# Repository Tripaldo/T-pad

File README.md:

# T-pad
my macropad, it has 8 buttons with macros that open apps and sites. every button has one or two led's linked to it so that they light up when the button is pressed. 

# Features
- 3d printed case
- led's linked to keys
- 8 keys
- simple python code with shortcuts to programs and sites

# CAD model
everything is held togheter by just 4 M3 bolts
the printed pieces are 2 and once the switches are soldered the keycaps will fit perfectly without any elevations.

made in fusion360.

# pcb
my pcb is very simple and made in KiCad.

this is the schematic:

this is the pcb:

# firmware
it uses KMK for a beginner friendly firmware.
- all 8 keys is a macro for apps and sites
- the firmware is easy to change so that everyone can change the macro's to whatever they like
- every button lights up the led near it
changes may be made in the future

# BOM
components needed for the hackpad (T-Pad)
- 8x cherry mx switches
- 8x dsa keycaps
- 4x M3 x 16 mm SHCS
- 12x SK6812 MINI
- 1x XIAO RP2040
- 1x case (only 3d printed parts)
  no need for diodes as it does not use a matrix but single digital pins
# extra
i have no idea what to tell you but it's my first project ever and hope it inspire someone

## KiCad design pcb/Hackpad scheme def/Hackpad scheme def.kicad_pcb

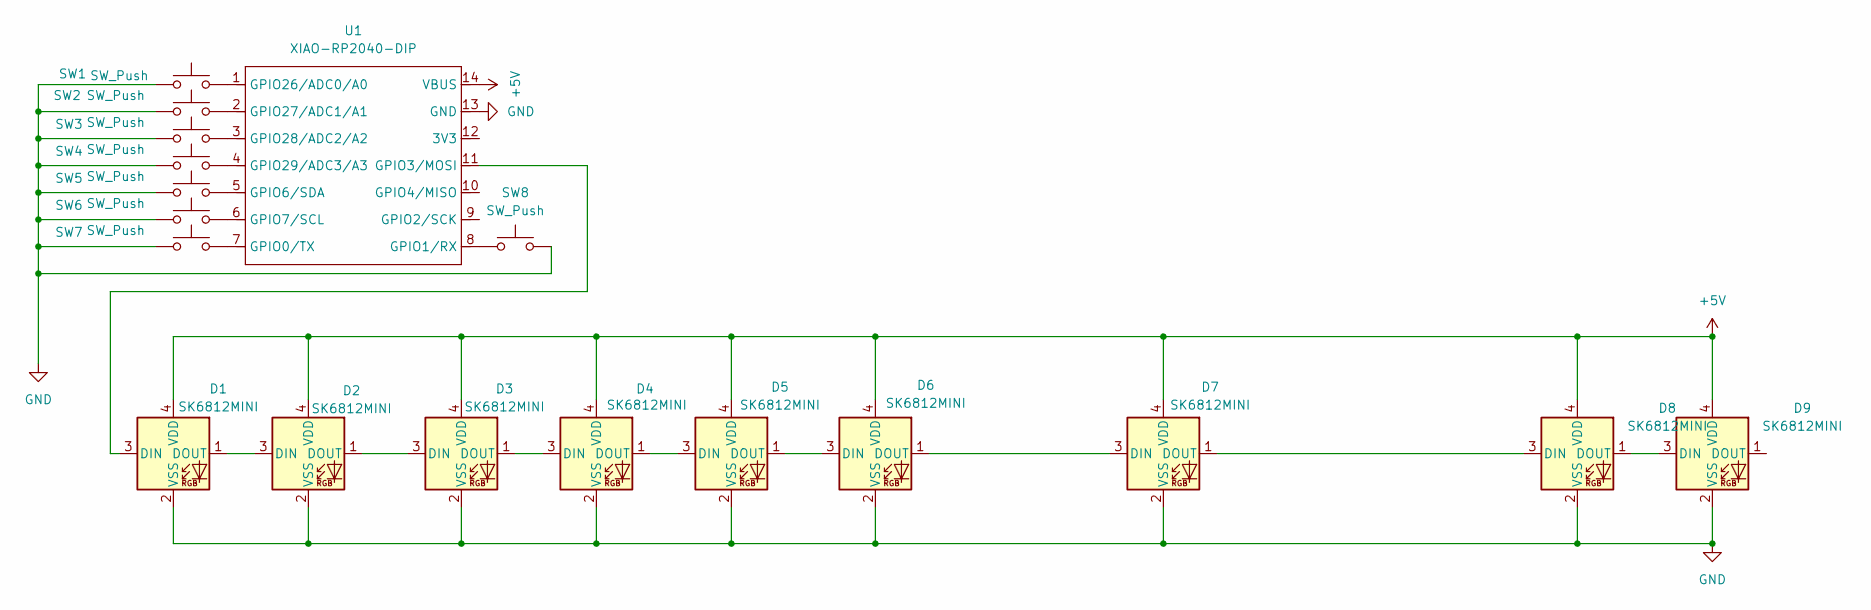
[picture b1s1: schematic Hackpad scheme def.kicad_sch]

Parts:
D1, D2, D3, D4, D5, D6, D7, D8, D9: SK6812MINI; LED_SK6812MINI_PLCC4_3.5x3.5mm_P1.75mm
SW1, SW2, SW3, SW4, SW5, SW6, SW7, SW8: SW_Push; SW_Cherry_MX_1.00u_PCB
U1: XIAO-RP2040-DIP

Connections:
+5V: D1.4 (VDD), D2.4 (VDD), D3.4 (VDD), D4.4 (VDD), D5.4 (VDD), D6.4 (VDD), D7.4 (VDD), D8.4 (VDD), D9.4 (VDD), U1.14 (VBUS)
GND: D1.2 (VSS), D2.2 (VSS), D3.2 (VSS), D4.2 (VSS), D5.2 (VSS), D6.2 (VSS), D7.2 (VSS), D8.2 (VSS), D9.2 (VSS), SW1.1, SW2.1, SW3.1, SW4.1, SW5.1, SW6.1, SW7.1, SW8.2, U1.13 (GND)
unnamed: D1.3 (DIN), U1.11 (GPIO3/MOSI)
unnamed: D1.1 (DOUT), D2.3 (DIN)
unnamed: D2.1 (DOUT), D3.3 (DIN)
unnamed: D3.1 (DOUT), D4.3 (DIN)
unnamed: D4.1 (DOUT), D5.3 (DIN)
unnamed: D5.1 (DOUT), D6.3 (DIN)
unnamed: D6.1 (DOUT), D7.3 (DIN)
unnamed: D7.1 (DOUT), D8.3 (DIN)
unnamed: D8.1 (DOUT), D9.3 (DIN)
unnamed: SW7.2, U1.7 (GPIO0/TX)
unnamed: SW8.1, U1.8 (GPIO1/RX)
unnamed: SW5.2, U1.5 (GPIO6/SDA)
unnamed: SW6.2, U1.6 (GPIO7/SCL)
unnamed: SW1.2, U1.1 (GPIO26/ADC0/A0)
unnamed: SW2.2, U1.2 (GPIO27/ADC1/A1)
unnamed: SW3.2, U1.3 (GPIO28/ADC2/A2)
unnamed: SW4.2, U1.4 (GPIO29/ADC3/A3)

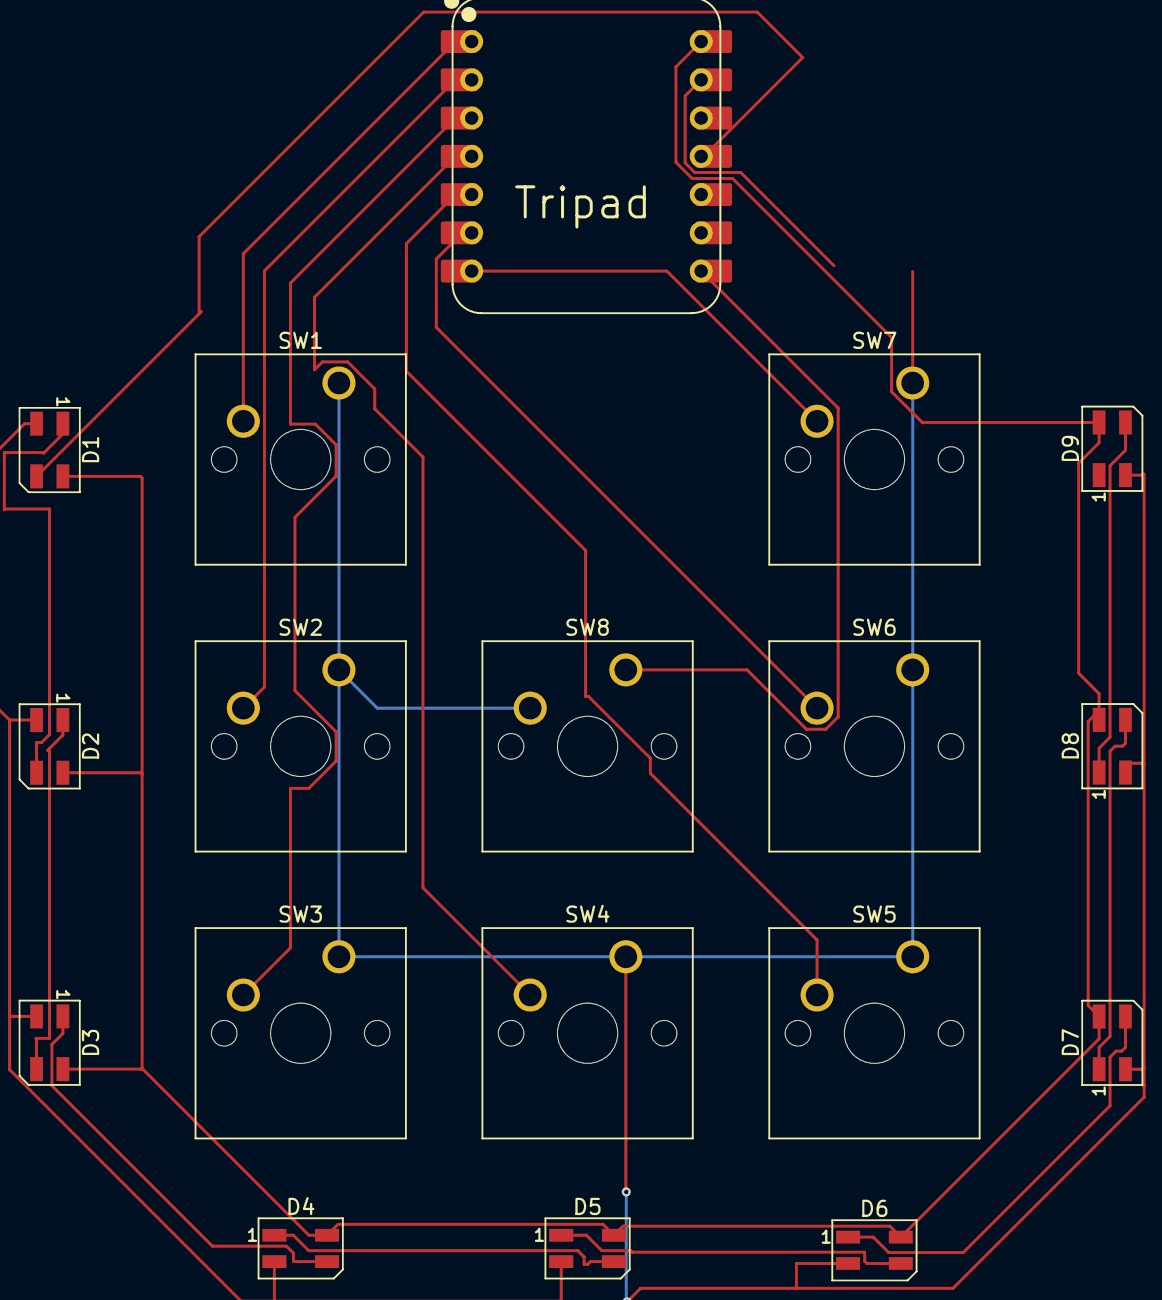
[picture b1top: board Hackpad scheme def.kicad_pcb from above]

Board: 2 copper layers, 18 parts (0 on the bottom side), 19 nets.
